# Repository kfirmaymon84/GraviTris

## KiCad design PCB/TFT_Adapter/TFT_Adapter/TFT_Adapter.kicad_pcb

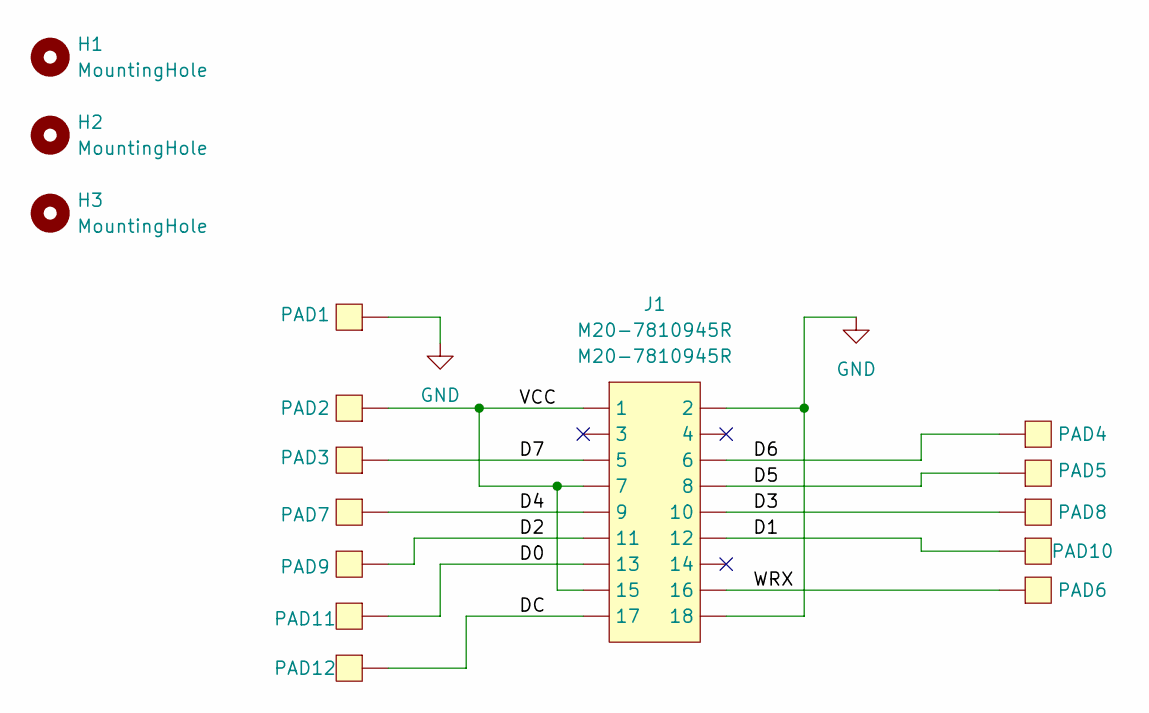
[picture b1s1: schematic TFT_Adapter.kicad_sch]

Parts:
H1, H2: MountingHole; MountingHole_2.2mm_M2
H3: MountingHole; 12mm_Hole_NoPad_1
J1: M20-7810945R; PartNumber M20-7810945R
PAD1, PAD2, PAD3, PAD4, PAD5, PAD6, PAD7, PAD8, PAD9, PAD10, PAD11, PAD12: PAD 2x1mm

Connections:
/D0: J1.13, PAD11.1
/D1: J1.12, PAD10.1
/D2: J1.11, PAD9.1
/D3: J1.10, PAD8.1
/D4: J1.9, PAD7.1
/D5: J1.8, PAD5.1
/D6: J1.6, PAD4.1
/D7: J1.5, PAD3.1
/DC: J1.17, PAD12.1
/VCC: J1.1, J1.7, J1.15, PAD2.1
/WRX: J1.16, PAD6.1
GND: J1.2, J1.18, PAD1.1

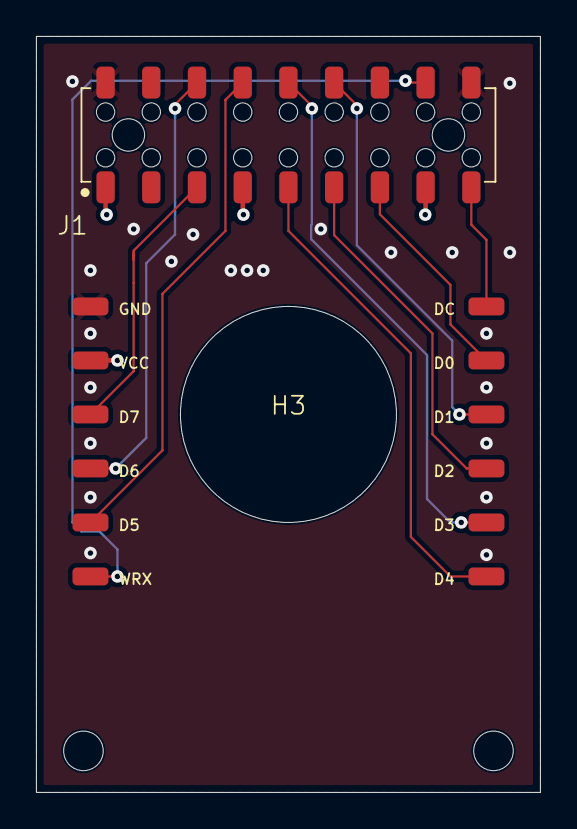
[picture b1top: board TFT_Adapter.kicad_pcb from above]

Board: 4 copper layers, 28.0 x 42.0 mm, 16 parts (0 on the bottom side), 12 nets.

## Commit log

2024-07-04 Add project files
2024-07-06 working on software
2024-07-07 update common functions
2024-07-07 Fix memory override while drawing to screen
    Fix memory override while drawing to screen
2024-07-09 Add draw power ups, fix draw score to remember last digits
2024-07-13 Start implementing game engine
2024-07-14 Update game engine to delete complete lines
2024-07-16 update game engine to be more efficient with display
2024-07-17 Update game score and Test on zynq
2024-07-18 add PCB and 3d files
2024-07-18 add hardware for I2c and buttons
2024-07-19 Disable Pull ups for MIO 50,51
2024-07-19 Add hardware 04
2024-07-19 reset hardware and add 05
2024-07-19 add 06
2024-07-19 Working on buttons
2024-07-20 Basic game start to work, need to fix Line recognition
2024-07-21 Add 3d files
2024-07-22 Add override_rotateScreen
2024-08-08 Add MIO buttons
2024-08-09 working on rotate display in game engine
2024-08-11 Add rotation to SDL Tester
2024-08-11 Arrage SDL Tester Code and add Comments.
2024-08-12 Add MLX90393 C code Port to Adafruit C++ example
2024-08-12 Add I2C initial to Zynq
2024-08-13 Add MLX90393 I2C Driver
2024-08-13 Marge game logic from SDL, Add display rotation
2024-08-14 Update display rotation logic
2024-08-14 Fix colors, Fix display spin.
2024-08-15 Ready for show
2024-08-18 Fir power ups count, next piece color
2026-02-19 Add version for vitis 25.1
2026-02-19 WIP lease enter the commit message for your changes. Lines starting
2026-02-19 Clean up git tracking: - update .gitignore with build/IDE/temp patterns - untrack generated ninja/CMake logs and workspace journal
    Also include start-screen tetromino preview changes and RNG seed logic
2026-02-19 Add input cooldown to slow piece movement
    - introduced moveCooldown and MOVE_DELAY_TICKS
    - apply movement only when cooldown expires
    - fix duplicate buttonsTick call earlier
2026-02-19 Add long-press on rotate ( 5s) to return to start screen
    - track rotateHoldTicks
    - compute threshold based on GAME_TICK_DELAY_MS
    - reset gameState and redraw start screen when triggered
2026-02-19 Reduce rotate-hold reset to 3s and fix auto-start bug
    - changed ROTATE_RESET_TICKS from 5000ms to 3000ms
    - added bWaitForSpinRelease flag to prevent immediate game start
    when returning to start screen with button still held
    - start screen now waits for button release before accepting input
2026-02-19 Fix: allow rotate button to start game on normal start screen
    - only clear bWaitForSpinRelease when spin is released
    - don't unconditionally set the flag on every spin press
    - now rotate button works normally to start game
